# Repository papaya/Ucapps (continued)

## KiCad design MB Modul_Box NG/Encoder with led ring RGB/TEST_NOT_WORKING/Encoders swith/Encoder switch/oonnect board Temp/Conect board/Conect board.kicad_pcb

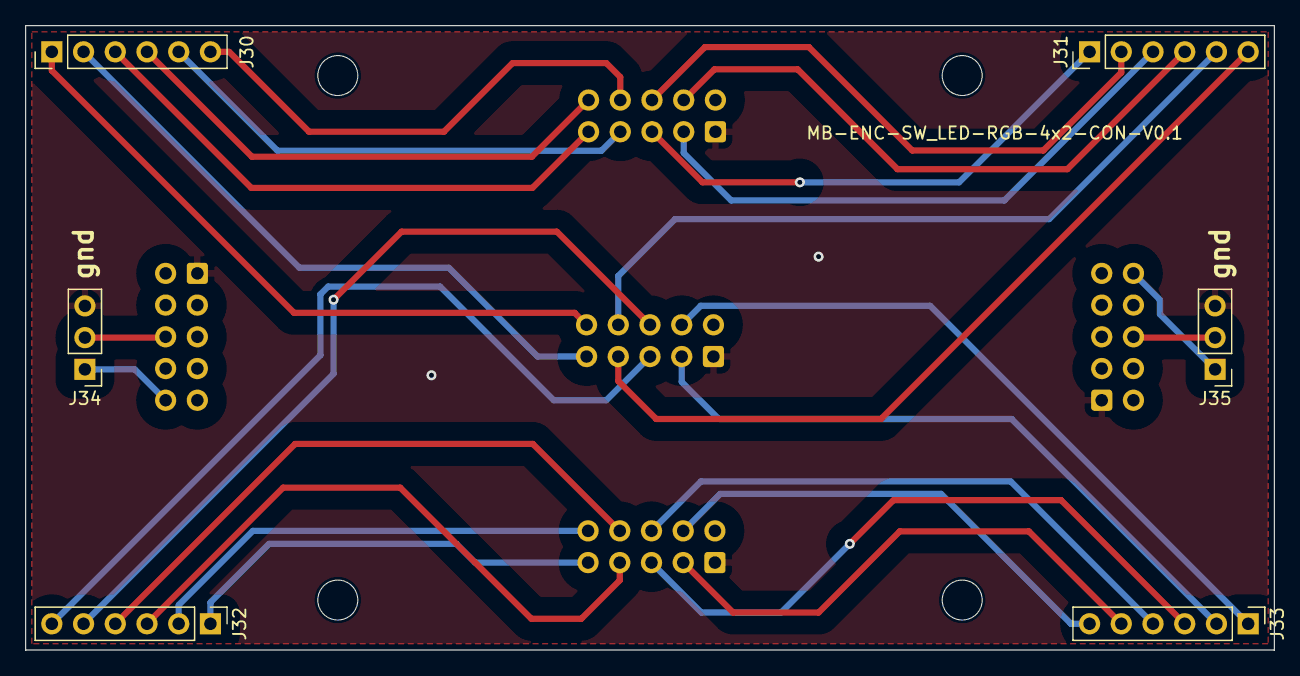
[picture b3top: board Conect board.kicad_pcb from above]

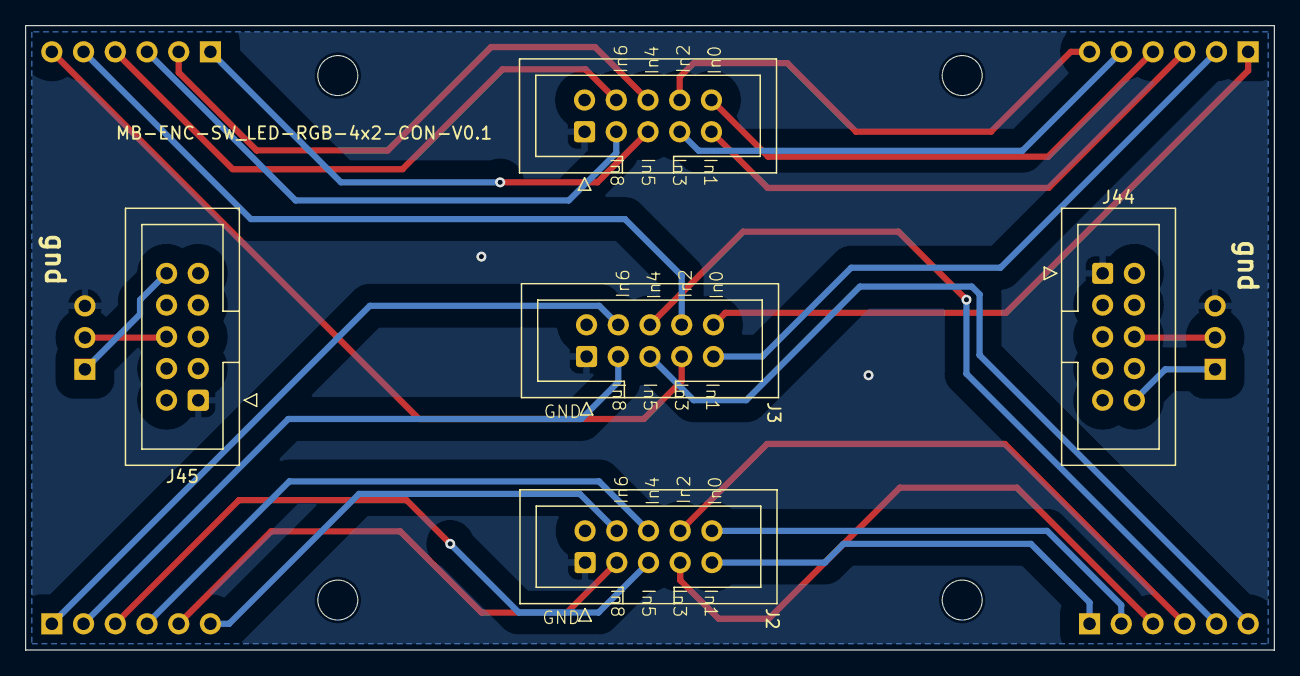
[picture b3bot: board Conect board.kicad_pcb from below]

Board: 2 copper layers, 100.0 x 50.0 mm, 15 parts (5 on the bottom side), 29 nets.

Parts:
H14, H16, H18, H20: MountingHole; MountingHole_3.2mm_M3
J1, J2, J3: sin_in; IDC-Header_2x05_P2.54mm_Vertical_ksr_dIN
J30, J31, J32, J33: Conn_01x06_Pin; PinHeader_1x06_P2.54mm_Vertical
J34, J35: Conn_01x06_Pin; PinHeader_1x03_P2.54mm_Vertical
J44, J45: IDC-Header_2x05_P2.54mm_Vertical

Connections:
+5VA: J34.1, J44.10
+5VD: J35.1, J45.10
C_ENC1A: J1.10, J30.4
C_ENC1B: J1.9, J30.3
C_ENC2A: J1.8, J30.6
C_ENC2B: J1.7, J30.5
C_ENC3A: J1.6, J31.2
C_ENC3B: J1.5, J31.1
C_ENC4A: J1.4, J31.4
C_ENC4B: J1.3, J31.3
C_ENC5A: J2.10, J32.2
C_ENC5B: J2.9, J32.1
C_ENC6A: J2.8, J32.4
C_ENC6B: J2.7, J32.3
C_ENC7A: J2.6, J33.4
C_ENC7B: J2.5, J33.3
C_ENC8A: J2.4, J33.6
C_ENC8B: J2.3, J33.5
C_SW1: J3.10, J30.1
C_SW2: J3.9, J30.2
C_SW3: J3.8, J31.5
C_SW4: J3.7, J31.6
C_SW5: J3.6, J32.5
C_SW6: J3.5, J32.6
C_SW7: J3.4, J33.1
C_SW8: J3.3, J33.2
GNDA: J1.1, J2.1, J3.1, J34.3, J35.3, J44.1, J45.1
unnamed: J34.2, J44.6
unnamed: J35.2, J45.6

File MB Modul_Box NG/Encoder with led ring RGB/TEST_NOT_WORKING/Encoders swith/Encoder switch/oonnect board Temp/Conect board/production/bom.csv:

Designator,Footprint,Quantity,Value,LCSC Part #
"H14, H16, H18, H20",MountingHole_3.2mm_M3,4,MountingHole,
"J1, J2, J3",IDC-Header_2x05_P2.54mm_Vertical_ksr_dIN,3,sin_in,
"J30, J31, J32, J33",PinHeader_1x06_P2.54mm_Vertical,4,Conn_01x06_Pin,
"J34, J35",PinHeader_1x03_P2.54mm_Vertical,2,Conn_01x06_Pin,
"J44, J45",IDC-Header_2x05_P2.54mm_Vertical,2,IDC-Header_2x05_P2.54mm_Vertical,

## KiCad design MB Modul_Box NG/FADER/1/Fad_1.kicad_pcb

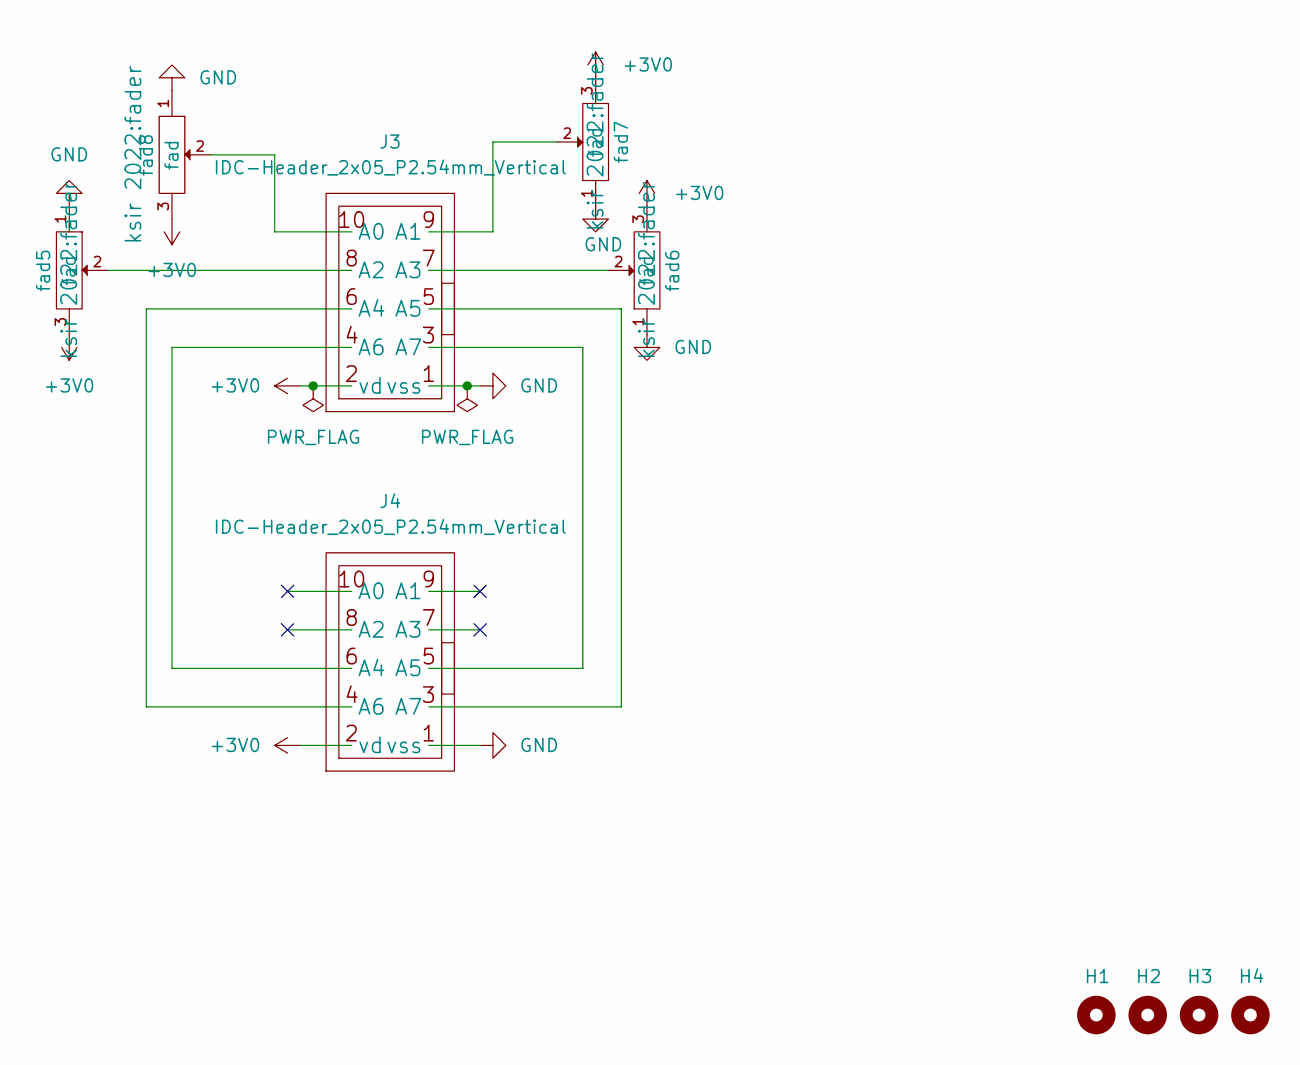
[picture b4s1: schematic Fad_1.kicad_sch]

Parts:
H1, H2, H3, H4: MountingHole; MountingHole_3.2mm_M3
J3, J4: IDC-Header_2x05_P2.54mm_Vertical
fad5, fad6, fad7, fad8: fad; fader

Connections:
+3V0: J3.2 (vd), J4.2 (vd), fad5.3 (vd), fad6.3 (vd), fad7.3 (vd), fad8.3 (vd)
GND: J3.1 (vss), J4.1 (vss), fad5.1 (vss_masse), fad6.1 (vss_masse), fad7.1 (vss_masse), fad8.1 (vss_masse)
unnamed: J3.10 (A0), fad8.2
unnamed: J3.9 (A1), fad7.2
unnamed: J3.8 (A2), fad5.2
unnamed: J3.7 (A3), fad6.2
unnamed: J3.6 (A4), J4.4 (A6)
unnamed: J3.5 (A5), J4.3 (A7)
unnamed: J3.4 (A6), J4.6 (A4)
unnamed: J3.3 (A7), J4.5 (A5)

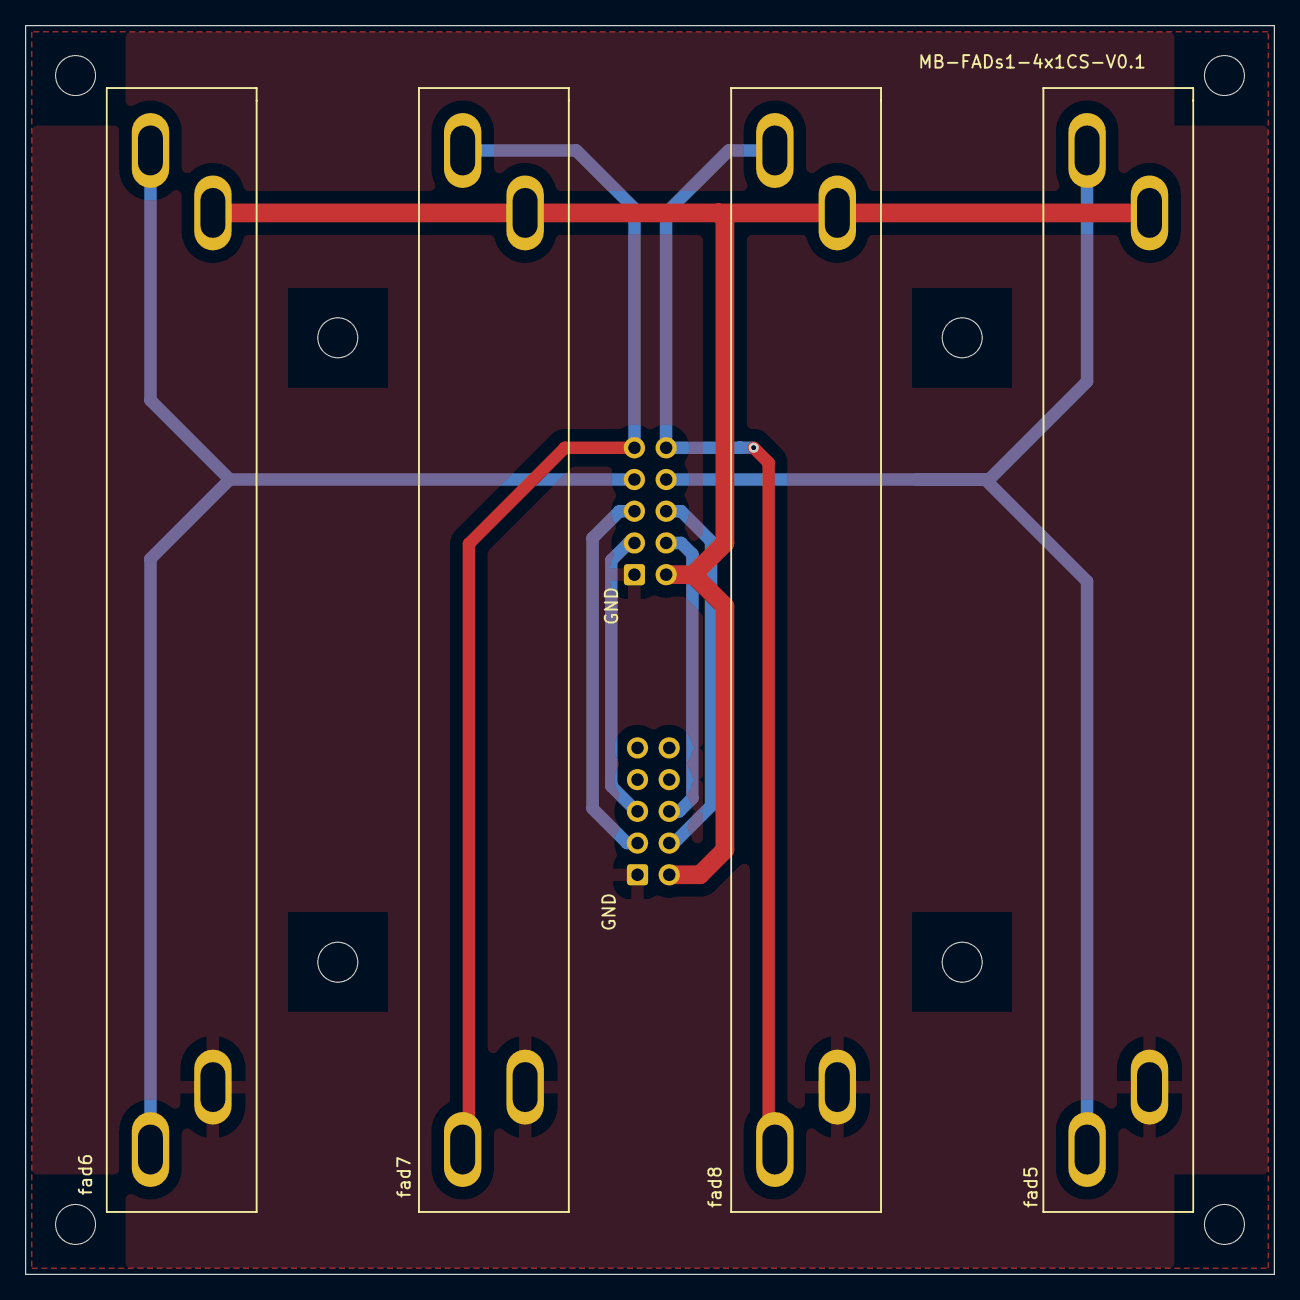
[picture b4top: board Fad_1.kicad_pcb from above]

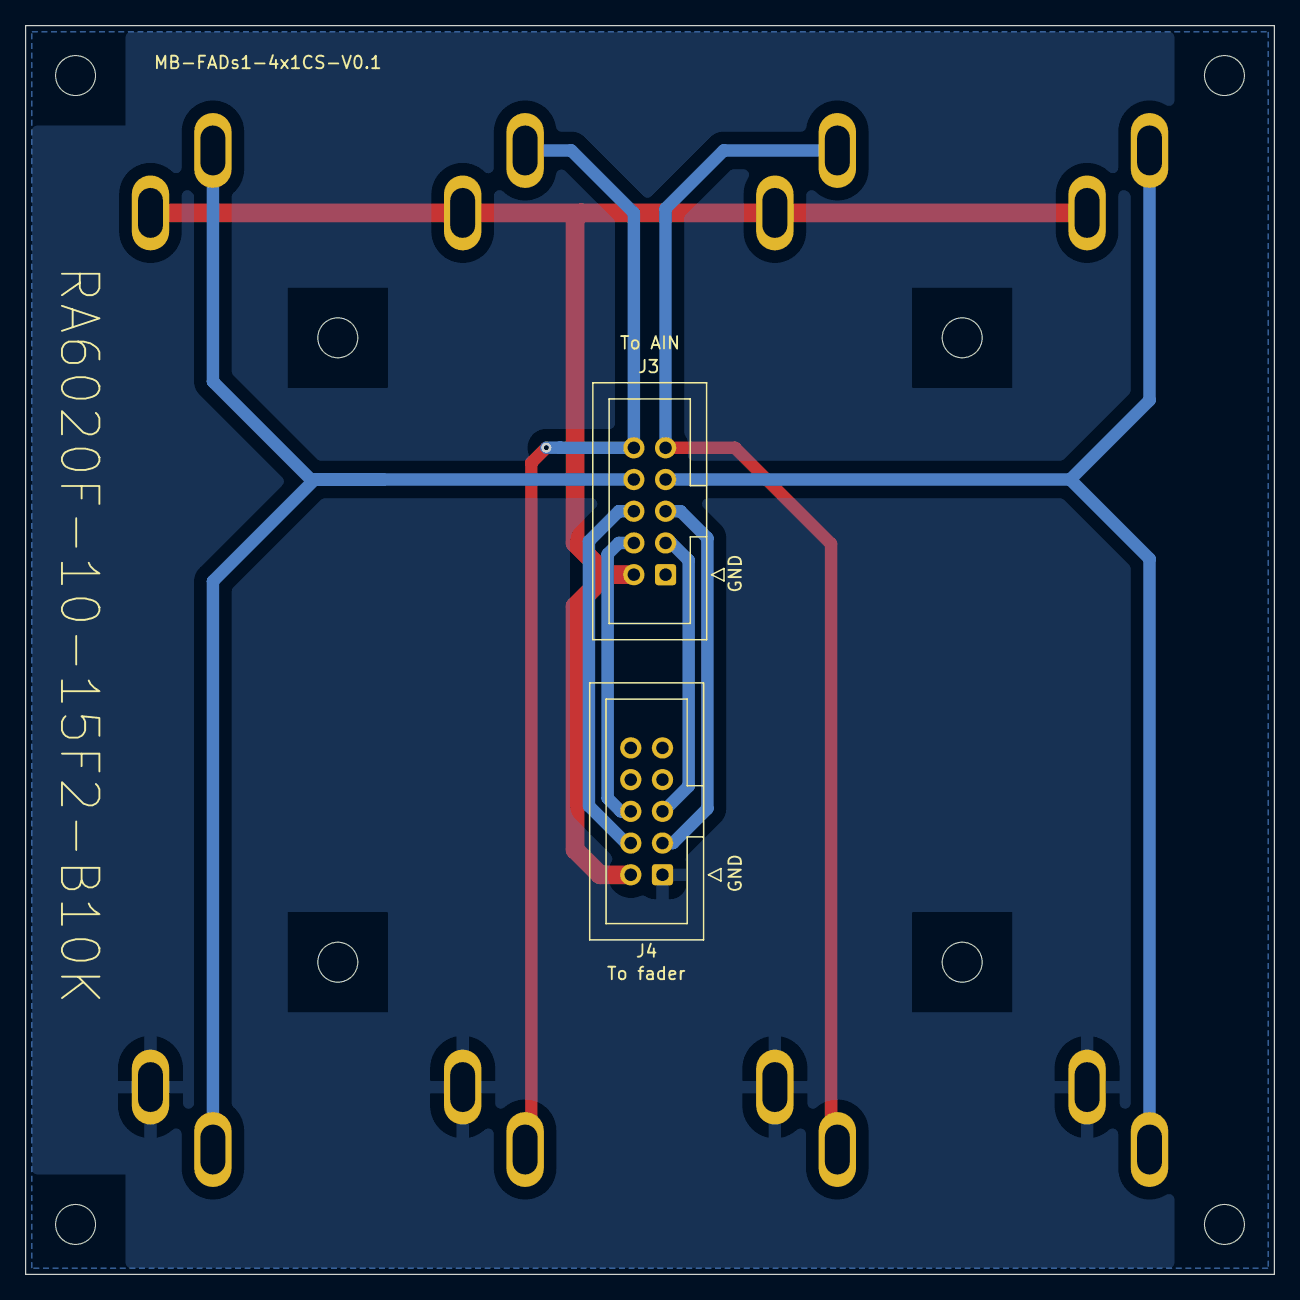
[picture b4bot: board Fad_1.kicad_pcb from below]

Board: 2 copper layers, 100.0 x 100.0 mm, 14 parts (2 on the bottom side), 10 nets.

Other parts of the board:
H1#2, H2#2, H3#2, H4#2: MountingHole; MountingHole_3.2mm_M3
